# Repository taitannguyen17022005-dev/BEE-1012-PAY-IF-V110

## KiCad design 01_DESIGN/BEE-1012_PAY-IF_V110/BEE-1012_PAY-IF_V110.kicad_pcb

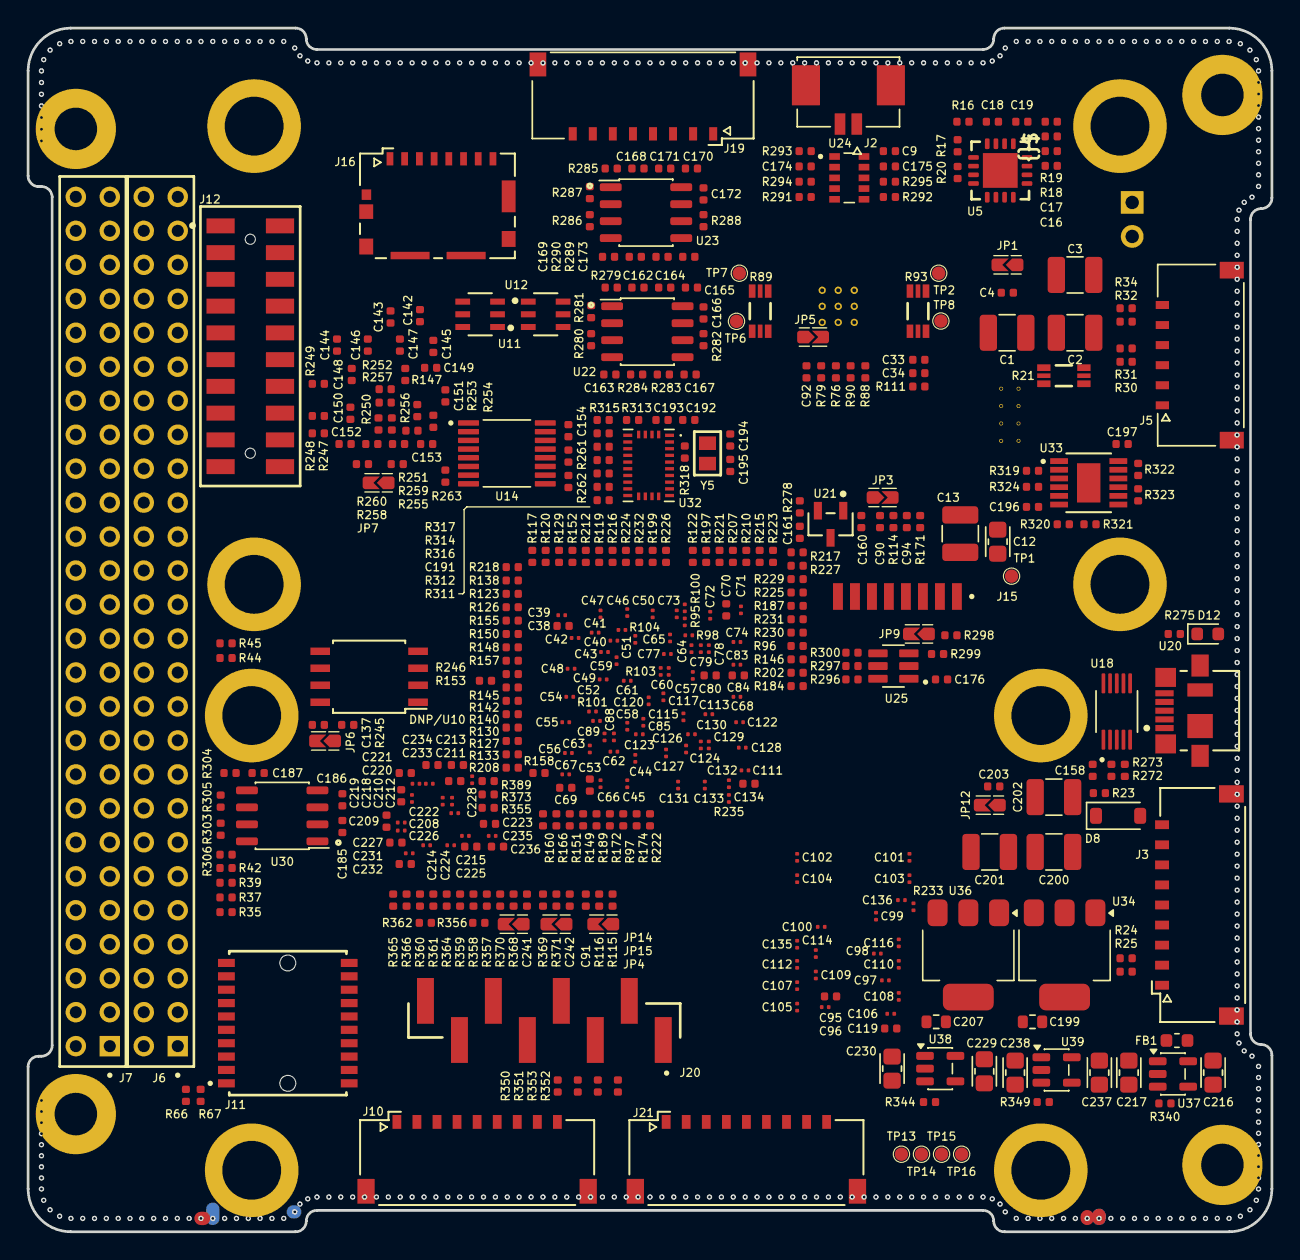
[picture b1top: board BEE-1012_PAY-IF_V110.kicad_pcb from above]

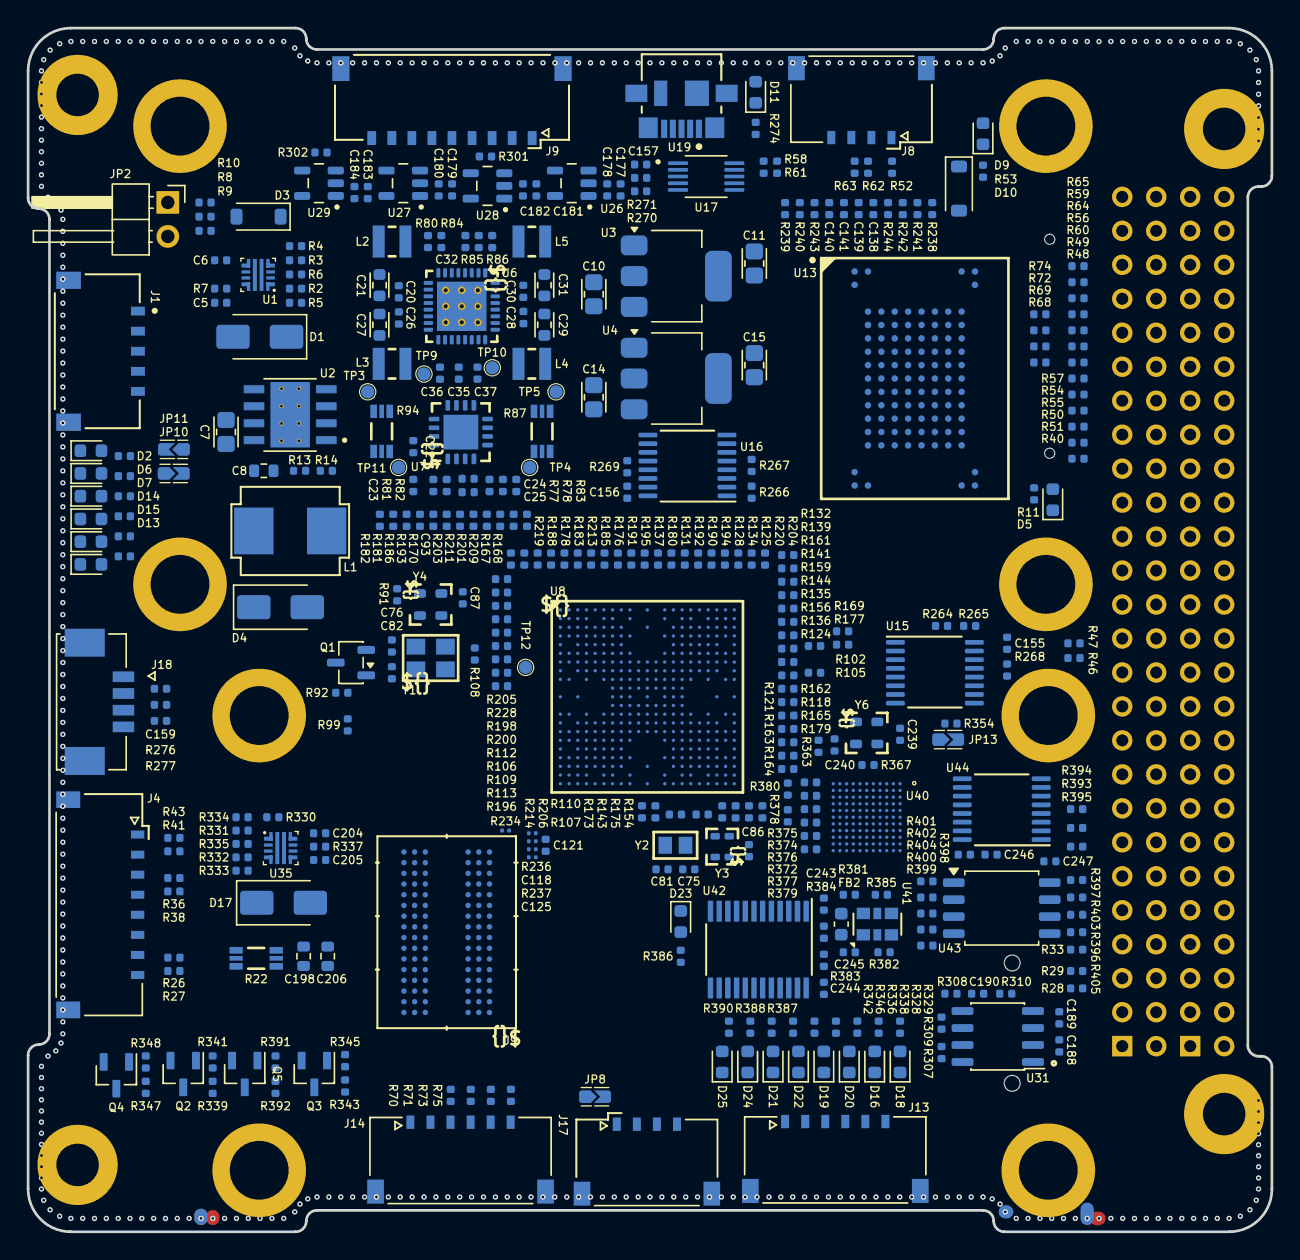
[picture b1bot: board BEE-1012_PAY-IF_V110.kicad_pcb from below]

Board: 8 copper layers, 93.0 x 90.0 mm, 803 parts (369 on the bottom side), 606 nets.

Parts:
C1, C2, C3, C13, C200, C201, C202: 47uF/25V; CAP_C_3225X80
C4, C140, C142, C160, C161, C164, C170, C176, C177, C179, C181, C183, C203: 1uF/20V; CAP_C_1005X50_L
C5, C6, C204, C205: 2.2nF/10V; CAP_C_1005X50_L
C7, C10, C11, C12, C14, C15: 10uF/20V; CAP_C_2012X110
C8: 0.01uF/16V; CAP_C_1608X80_L
C9, C16, C18, C22, C24, C32, C33, C34, C86, C87, C90, C91, C93, C94, C137, C138, C139, C141, C143, C146, C147, C148, C149, C150, C151, C152, C153, C154, C155, C156, C157, C158, C159, C162, C163, C165, C166, C167, C168, C169, C171, C172, C173, C174, C175, C185, C186, C187, C188, C189, C190, C191, C192, C193, C196, C197, C239, C240, C241, C242, C243, C244, C245, C246, C247: 0.1uF/10V; CAP_C_1005X50_L
C17, C19, C20, C23, C25, C26, C28, C30, C35, C36, C37, C38, C53, C69, C70, C80, C84, C95, C119, C121, C134, C144, C145, C209, C211, C213, C219, C221, C223, C225, C227, C232, C234, C236: 4.7uF/10V; CAP_C_1005X50_L
C21, C27, C29, C31: 22uF/10V; CAP_C_1608X80
C39, C40, C41, C42, C43, C44, C45, C46, C47, C48, C49, C50, C51, C52, C54, C55, C56, C57, C58, C59, C60, C61, C62, C63, C64, C65, C66, C67, C68, C71, C72, C73, C74, C77, C78, C79, C83, C85, C88, C89, C96, C97, C98, C99, C100, C101, C102, C103, C104, C105, C106, C107, C108, C109, C110, C111, C112, C113, C114, C115, C116, C117, C118, C120, C122, C123, C124, C125, C126, C127, C128, C129, C130, C131, C132, C133, C135, C136, C208, C210, C212, C214, C215, C218, C220, C222, C224, C226, C228, C231, C233, C235: 0.1uF/10V; CAP_C_0603x30
C75, C76, C81, C82, C194, C195: 18pF/10V; CAP_C_1005X50_L
C92: 2.2uF/10V; CAP_C_1005X50_L
C178, C180, C182, C184: 0.1uF/20V; CAP_C_1005X50_L
C198, C199, C206, C207: 10uF/20V; CAP_C_1608X80_L
C216, C217, C229, C230, C237, C238: 4.7uF/10V; CAP_C_2012X110
D1, D4, D17: SS54; D_SMA
D2, D15, D18, D25: LED_RED; LED_0603_1608Metric
D3, D8, D10: 1N4148W-TP; D_SOD-123
D5, D7, D14, D16, D19, D20, D21, D22, D23, D24: LED_GREEN; LED_0603_1608Metric
D6: LED_YELLOW; LED_0603_1608Metric
D9, D11, D12, D13: LED_BLUE; LED_0603_1608Metric
DNP/U10: AS3004204-0108X0PSAY; SOIC127P790X216-8
FB1, FB2: BLM18PG121SN1D; L_0603_1608Metric
H1, H2, H3, H4, H5, H6, H7, H8: 9774060360R; M4.4
Hole1, Hole2, Hole3, Hole4: hole_space; HEX-M3_NoVia
J1: 5040500591
J2: 0532610271; MOLEX_0532610271
J3, J9, J10, J21: 5040500991; MOLEX_5040500991
J4, J19: 5040500891; MOLEX_5040500891
J5, J13, J14: 5040500691; MOLEX_5040500691
J6, J7: ESQ-126-14-G-D
J8, J17: 5040500491; MOLEX_5040500491
J11: FSI-110-03-G-D-AD; SAMTEC_FSI-110-03-X-D-AD-TR
J12: TLE-110-01-G-DV-A-TR; SAMTEC-TLE-110-01-X-DV-A
J15: Header 8x1; PAD JTAG 1.27
J16: Molex_1051620001; MOLEX_1051620001
J18: 0532610471; MOLEX_0532610471
J20: HEADER 8x1; SAMTEC_TSM-108-01-L-SV-P-TR
JP1, JP8, JP9, JP10, JP11, JP12, JP13: Jumper_2_Bridged; JUMPER_1608
JP2: JUMPER_254P_NOPLACE; PinHeader_1x02_P2.54mm_Horizontal
JP3, JP7, JP15: Reset button; JUMPER_1608
JP4, JP14: User button; JUMPER_1608
JP5: nSTART button; JUMPER_1608
JP6: JUMPER_1608
L1: SRP7050TA-220M
L2, L3, L4, L5: DFE252012P-1R5M=P2; IND_C_1008
Q1: BSS138; SOT-23-3
Q2, Q3, Q4, Q5: MMBT2222A; SOT95P240X120-3N
R1, R66, R67, R77, R78, R245, R261, R262, R263, R264, R265, R266, R267, R270, R271, R272, R273, R293, R294, R295, R311, R312, R315, R316, R319, R320, R324, R350, R351, R352, R353, R389, R393, R394, R395, R399: 4.7k; RES_C_1005x30_L
R2, R331: 470k; RES_C_1005x30_L
R3, R4, R6, R152, R332, R333, R348: 47k; RES_C_1005x30_L
R5, R8, R13, R18, R19, R20, R52, R81, R82, R85, R86, R90, R91, R92, R115, R170, R171, R177, R238, R239, R240, R241, R242, R243, R244, R247, R248, R249, R250, R251, R252, R253, R254, R255, R256, R257, R260, R268, R269, R276, R277, R281, R284, R287, R290, R306, R310, R313, R334, R339, R340, R341, R343, R344, R345, R347, R349, R368, R369, R381, R382, R383, R384, R390, R391, R392, R398: 10k; RES_C_1005x30_L
R7, R337: 1.6k; RES_C_1005x30_L
R9, R11, R12, R15, R23, R53, R80, R258, R274, R275, R325, R326, R327, R328, R336, R338, R342, R346, R354, R363, R386, R387, R388: 1k; RES_C_1005x30_L
R10, R14, R329: 3.24k; RES_C_1005x30_L
R16, R17, R48, R49, R64, R65, R291, R292, R314, R317, R321, R396, R397, R400: DNP/4.7k; RES_C_1005x30_L
R21, R22, R87, R89, R93, R94: Shunt 4 Pin; RES_C_1206_SHUNT
R24, R25, R30, R31, R32, R34, R35, R37, R39, R42, R56, R57, R58, R59, R60, R61, R76, R79, R83, R106, R109, R355, R357, R358, R359, R360, R361, R364, R365, R366, R372, R373, R374, R375, R376, R377, R379, R401, R402, R403, R404, R405: 0R; RES_C_1005x30_L
R26, R27, R28, R29, R33, R36, R38, R40, R41, R43, R44, R45, R46, R47, R50, R51, R54, R55, R62, R63, R68, R69, R70, R71, R72, R73, R74, R75, R110, R111, R113: DNP/0R; RES_C_1005x30_L
R84: 100k; RES_C_1005x30_L
R88, R97, R167, R168, R169, R181, R182, R186, R193, R201, R203, R209, R211, R330: DNP/10k; RES_C_1005x30_L
R95, R98, R100: 200R; RES_C_0603X30
R96: 10K; RES_C_1005x30_L
R99, R114, R116, R259, R301, R302, R356, R362, R370, R371, R378, R380: 100R; RES_C_1005x30_L
R101, R104: 16.9k; RES_C_0603X30
R102: 20k; RES_C_1005x30_L
R103: 20k; RES_C_0603X30
R105: 4.02k; RES_C_1005x30_L
R107, R108: 1M 1%; RES_C_1005x30_L
R112, R367: DNP/22R; RES_C_1005x30_L
R117, R118, R119, R120, R121, R122, R123, R124, R125, R126, R127, R128, R129, R130, R131, R132, R133, R134, R135, R136, R137, R138, R139, R140, R141, R142, R143, R144, R145, R146, R147, R148, R149, R150, R151, R153, R154, R155, R156, R157, R158, R159, R160, R161, R162, R163, R164, R165, R166, R172, R173, R174, R175, R176, R178, R179, R180, R183, R184, R185, R187, R188, R189, R190, R191, R192, R194, R195, R196, R197, R198, R199, R200, R202, R204, R205, R206, R207, R208, R210, R212, R213, R214, R215, R216, R217, R218, R219, R220, R221, R222, R223, R224, R225, R226, R227, R228, R229, R230, R231, R232, R278, R279, R280, R282, R283, R285, R286, R288, R289, R296, R297, R300, R304, R308: 22R; RES_C_1005x30_L
R233, R235: 240R; RES_C_0603X30
R234: 100k; RES_C_0603X30
R236, R237: 1k; RES_C_0603X30
R246: 120R; RES_C_1005x30_L
R298, R299: 16.5k; RES_C_1005x30_L
R303, R305, R307, R309: 60R; RES_C_1005x30_L
R318: DNP/1M 1%; RES_C_1005x30_L
R322, R323: DNP/120R; RES_C_1005x30_L
R335: 133k; RES_C_1005x30_L
R385: DNP/100R; RES_C_1005x30_L
TP1, TP2, TP3, TP4, TP5, TP6, TP7, TP8, TP9, TP10, TP11, TP12, TP13, TP14, TP15, TP16: VALUE; Test point
U1, U35: TPS259470ARPWR; VQFN-HR-10
U2: TPS5430DDAR; CONV_TPS5430DDAR
U3, U4, U34, U36: LM1117MP-3.3/NOPB; SOT-223
U5: PAC1934; UQFN-16_4X4_EP2.6X2.6
U6: MCP16502 QFN-32; QFN-32_5X5_EP3.7X3.7
U7: Microchip PAC1934 UQFN-16; UQFN-16_4X4_EP2.6X2.6
U8: SAMA7G54; TFBGA-343_14x14 - 2.5mm
U9: IS43TR16512BL-125KBLI; TWBGA96_ISI
U11, U12: IP4220CZ6; DIODE_SOT457_1P7X3P1_NEX
U13: MTFC32GAZAQDW-AAT; BGA_100_C_100P_10X17_1400X1800X150
U14: SN74LV4052APWR; SOP65P640X120-16N
U15, U16, U44: SN3257QPWRQ1; SOIC_PRQ1_TEX
U17, U18: FSUSB42MUX; SOP50P490X110-10N
U19, U20: 473460001; 47346-0001_MOL
U21: TC1047AVNBTR; SOT-23_MC_MCH
U22, U23: OPA2340; SOIC127P602X173-8N
U24: RV-3129-C3-32.768KHZ-OPTION-A-TB-QA; IC_RV-3129-C3-32.768KHZ-OPTION-A-TB-QA
U25: TPL5010DDCR
U26, U27: DS90LV011AQ-Q1
U28, U29: DS90LT012AQ-Q1; DS90LV011AQ-Q1
U30, U31: SN65HVD230DR; SOIC127P602X173-8N
U32: BNO086; IC_BNO086
U33: LTC2865HMSE#TRPBF; MSOP-12_MSE_LIT
U37, U38: TLV75518PDBVR; SOT-23-5
U39: TLV75510PDBVR; SOT-23-5
U40: LFD2NX-17-7MG121I; csfBGA121_LAT
U41: DSC1123CI1-050.0000; VDFN6_3P2X2P5_MCH
U42: SN74AXCH8T245PWR; SOP65P640X120-24N
U43: S25FL128LAGMFI010; SOIC-8_5.3x5.3mm_P1.27mm
Y1: 24MHz; CRYSTAL_ABM8G
Y2, Y5: 32.768kHz; CRYSTAL_NX2012SA
Y3: 32.768KHz; DFN-4_2x1.6
Y4, Y6: DSC10xx DFN-4; DFN-4_2.5x2

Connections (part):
1V8_VCCAUX: C208.2, C209.1, C210.2, C211.1, C212.2, C213.1, C214.2, C215.2, C216.1, R339.2, U37.5 (OUT), U40.C6 (VCCAUXA), U40.D9 (VCCAUXH5), U40.F3 (VCCAUX), U40.H3 (VCCAUXH3), U40.H8 (VCCAUXH4)
1V8_VCCIO3/4/5: C222.2, C223.1, C224.2, C225.1, C226.2, C227.1, C228.2, C229.1, C243.2, R343.2, R368.2, R369.2, R381.1, U38.5 (OUT), U40.E8 (VCCIO5), U40.J6 (VCCIO3), U40.J9 (VCCIO4), U40.K3 (VCCIO3), U42.1 (VCCA)
1V_VCORE: C231.2, C232.1, C233.2, C234.1, C235.2, C236.1, C237.1, R347.2, U39.5 (OUT), U40.C10 (VCC), U40.E4 (VCC), U40.G6 (VCCECLK)
3.3_VBAT: C9.2, C175.2, J2.1, R111.1, U24.9 (VBACKUP)
3V3_COM: C15.1, C154.2, C155.2, C156.2, C157.2, C158.2, C159.2, C160.2, C164.2, C165.2, C170.2, C171.2, C174.2, C176.2, C177.2, C178.2, C179.2, C180.2, C181.2, C182.2, C183.2, C184.2, C185.2, C186.2, C188.2, C189.2, C192.2, C193.2, C196.2, C197.2, C244.2, C246.2, C247.2, J11.03, J11.04, J11.17, J11.18, J12.2, J18.1, J19.1, J19.3, J19.5, J19.7, R15.1, R48.2, R49.2, R64.2, R65.2, R66.2, R67.2, R264.1, R265.1, R266.1, R267.1, R276.1, R277.1, R291.1, R292.1, R293.1, R294.1, R295.1, R311.1, R312.1, R313.1, R314.1, R315.1, R319.1, R320.1, R393.1, R394.1, R395.1, R396.1, R397.1, R399.1, R400.1, U4.2 (VOUT_2), U4.4 (VOUT_4), U14.16 (VCC), U15.16 (VDD), U16.16 (VDD), U17.1 (VCC), U18.1 (VCC)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
3V3_FPGADN: C207.1, C230.1, C238.1, R336.1, R342.1, R344.1, R346.1, R349.1, U36.2 (VOUT_2), U36.4 (VOUT_4), U38.1 (IN), U39.1 (IN)
3V3_FPGAUP: C199.1, C217.1, FB1.2, R328.1, R338.1, R340.1, U34.2 (VOUT_2), U34.4 (VOUT_4), U37.1 (IN)
3V3_VCCIO0/1: C218.2, C219.1, C220.2, C221.1, C239.1, C240.2, C245.2, FB1.1, FB2.2, J20.2, R350.1, R351.1, R352.1, R354.1, R363.1, R382.2, R387.1, R388.1, R389.1, R390.2, R392.2, U40.D2 (VCCIO1), U40.D4 (VCCIO0), Y6.4 (VDD)
3V3_eMMC: C11.1, C138.2, C139.2, C140.2, C141.2, C144.1, C145.1, C146.2, C147.2, C148.2, C149.2, C150.2, C151.2, C152.2, C153.2, J16.P4 (VDD), R11.1, R238.1, R239.1, R240.1, R241.1, R242.1, R243.1, R244.1, R247.1, R248.1, R249.1, R250.1, R251.1, R252.1, R253.1, R254.1, R255.1, R256.1, R257.1, R258.1, U3.2 (VOUT_2), U3.4 (VOUT_4), U11.5 (VBUS), U12.5 (VBUS), U13.F2 (VCC), U13.F3 (VCC), U13.F4 (VCC), U13.F5 (VCC), U13.F6 (VCC), U13.F7 (VCC), U13.F8 (VCC), U13.F9 (VCC), U13.H3 (VCCQ), U13.H8 (VCCQ), U13.L2 (VCCQ), U13.L4 (VCCQ), U13.L7 (VCCQ), U13.L9 (VCCQ), U13.P3 (VCCQ), U13.P8 (VCCQ)
5V: C10.1, C12.1, C13.1, C14.1, C20.1, C26.1, C28.1, C30.1, C32.2, C35.1, C202.1, C203.2, JP8.1 (A), JP12.1 (A), L1.2, R12.1, R13.1, R88.1, R169.1, R330.1, R331.1, TP1.1 (1_1), U3.3 (VIN), U4.3 (VIN), U6.4 (SVIN), U6.10 (PVIN1), U6.15 (PVIN2), U6.20 (LVIN), U6.26 (PVIN3), U6.31 (PVIN4), U35.5 (IN)
5V_FPGA: C198.1, C206.1, R22.2, U34.3 (VIN), U36.3 (VIN)
5V_FPGA_efuse: C200.1, C201.1, D17.1 (K), JP12.2 (B), R22.1, R329.1, R332.1, R333.1, U35.6 (OUT)
12V: C7.1, R21.2, U2.7 (VIN)
12V_CONN: C3.1, C4.2, J1.1, J1.2, J3.1, J3.2, J3.3, JP1.1 (A), R2.1, R8.1, U1.5 (IN)
12V_efuse: C1.1, C2.1, D1.1 (K), JP1.2 (B), R1.1, R3.1, R4.1, R21.1, U1.6 (OUT)
/CONNECTOR_EXP/EXP_ON_IF: D8.2 (A), J3.7
/CONNECTOR_EXP/EXP_USB_N: J4.8, R25.1, R27.1
/CONNECTOR_EXP/EXP_USB_P: J4.7, R24.1, R26.1
/CONNECTOR_INTERFACE/CLK_EXP_CONNECTOR: J14.4, R71.2
/CONNECTOR_INTERFACE/CONN_422_RX_N: J5.5, R32.2
/CONNECTOR_INTERFACE/CONN_422_RX_P: J5.6, R34.2
/CONNECTOR_INTERFACE/CONN_422_TX_N: J5.4, R31.2
/CONNECTOR_INTERFACE/CONN_422_TX_P: J5.3, R30.2
/CONNECTOR_INTERFACE/CS_EXP_CONNECTOR: J14.3, R70.2
/CONNECTOR_INTERFACE/IF_USB_CONN_N: J8.2, R58.2, R62.2
/CONNECTOR_INTERFACE/IF_USB_CONN_P: J8.3, R61.2, R63.2
/CONNECTOR_INTERFACE/MISO_EXP_CONNECTOR: J14.6, R75.2
/CONNECTOR_INTERFACE/MOSI_EXP_CONNECTOR: J14.5, R73.2
/CONNECTOR_INTERFACE/SCL_EXP_CONNECTOR: J13.5, J13.6, R72.2, R74.2
/CONNECTOR_INTERFACE/SDA_EXP_CONNECTOR: J13.1, J13.2, R68.2, R69.2
/FPGA_PART1/JTAG_EN: JP13.2 (B), R354.2, U40.A1 (JTAG_EN)
/FPGA_PART1/JTAG_TCK: J20.5, R353.1, U40.C1 (PR9A)
/FPGA_PART1/JTAG_TDI: J20.4, R352.2, U40.A3 (PR5A)
/FPGA_PART1/JTAG_TDO: J20.7, R351.2, U40.A2 (PR5B)
/FPGA_PART1/JTAG_TMS: J20.8, R350.2, U40.B1 (PR3B)
/FPGA_POWER/AUXOFF: R332.2, U35.3 (PG/AUXOFF)
/FPGA_POWER/~FLT: R333.2, U35.4 (PGTH/~FLT)
/IMU/BNO_PS0: R314.2, R316.1, U32.6 (PS0/WAKE)
/IMU/BNO_PS1: R315.2, R317.1, U32.5 (PS1)
/IMU/BNO_XIN32: C194.1, R318.1, U32.27 (XIN32), Y5.2
/IMU/BNO_XOUT32: C195.1, R318.2, U32.26 (XOUT32/CLKSEL1), Y5.1
/POWER/AUXOFF: R3.2, U1.3 (PG/AUXOFF)
/POWER/~FLT: R4.2, U1.4 (PGTH/~FLT)
/POWER_MEASUREMENT/SENSE_5V_FPGA_N: R22.4, U5.14 (SENSE2-)
/POWER_MEASUREMENT/SENSE_5V_FPGA_P: R22.3, U5.13 (SENSE2+)
/POWER_MEASUREMENT/SENSE_12V_EXP_N: R21.4, U5.12 (SENSE1-)
/POWER_MEASUREMENT/SENSE_12V_EXP_P: R21.3, U5.11 (SENSE1+)
/SAMA7G54_DDR3L/DDR_A0: U8.W6 (DDR_A0), U9.N3 (A0)
/SAMA7G54_DDR3L/DDR_A1: U8.P6 (DDR_A1), U9.P7 (A1)
/SAMA7G54_DDR3L/DDR_A2: U8.V5 (DDR_A2), U9.P3 (A2)
/SAMA7G54_DDR3L/DDR_A3: U8.V6 (DDR_A3), U9.N2 (A3)
/SAMA7G54_DDR3L/DDR_A4: U8.R6 (DDR_A4), U9.P8 (A4)
/SAMA7G54_DDR3L/DDR_A5: U8.W4 (DDR_A5), U9.P2 (A5)
/SAMA7G54_DDR3L/DDR_A6: U8.P7 (DDR_A6), U9.R8 (A6)
/SAMA7G54_DDR3L/DDR_A7: U8.W2 (DDR_A7), U9.R2 (A7)
/SAMA7G54_DDR3L/DDR_A8: U8.L8 (DDR_A8), U9.T8 (A8)
/SAMA7G54_DDR3L/DDR_A9: U8.V4 (DDR_A9), U9.R3 (A9)
/SAMA7G54_DDR3L/DDR_A10: U8.T3 (DDR_A10), U9.L7 (A10/AP)
/SAMA7G54_DDR3L/DDR_A11: U8.M9 (DDR_A11), U9.R7 (A11)
/SAMA7G54_DDR3L/DDR_A12: U8.P5 (DDR_A12), U9.N7 (A12/BC#)
/SAMA7G54_DDR3L/DDR_A13: U8.V2 (DDR_A13), U9.T3 (A13)
/SAMA7G54_DDR3L/DDR_A14: U8.L9 (DDR_A14), U9.T7 (A14)
/SAMA7G54_DDR3L/DDR_A15: U8.R4 (DDR_A15), U9.M7 (A15)
/SAMA7G54_DDR3L/DDR_BA0: U8.V8 (DDR_BA0), U9.M2 (BA0)
/SAMA7G54_DDR3L/DDR_BA1: U8.P4 (DDR_BA1), U9.N8 (BA1)
/SAMA7G54_DDR3L/DDR_BA2: U8.R8 (DDR_BA2), U9.M3 (BA2)
/SAMA7G54_DDR3L/DDR_CAS: U8.T8 (DDR_CAS#), U9.K3 (CAS#)
/SAMA7G54_DDR3L/DDR_CKE: U8.V3 (DDR_CKE), U9.K9 (CKE)
/SAMA7G54_DDR3L/DDR_CK_N: U8.T4 (DDR_CLK_N), U9.K7 (CK#)
/SAMA7G54_DDR3L/DDR_CK_P: U8.U4 (DDR_CLK_P), U9.J7 (CK)
/SAMA7G54_DDR3L/DDR_CS: U8.V7 (DDR_CS#), U9.L2 (CS#)
/SAMA7G54_DDR3L/DDR_D0: U8.N2 (DDR_D0), U9.E3 (DQL0)
/SAMA7G54_DDR3L/DDR_D1: U8.M7 (DDR_D1), U9.F7 (DQL1)
/SAMA7G54_DDR3L/DDR_D2: U8.R3 (DDR_D2), U9.F2 (DQL2)
/SAMA7G54_DDR3L/DDR_D3: U8.M8 (DDR_D3), U9.F8 (DQL3)
/SAMA7G54_DDR3L/DDR_D4: U8.T2 (DDR_D4), U9.H3 (DQL4)
/SAMA7G54_DDR3L/DDR_D5: U8.N8 (DDR_D5), U9.H8 (DQL5)
/SAMA7G54_DDR3L/DDR_D6: U8.T1 (DDR_D6), U9.G2 (DQL6)
/SAMA7G54_DDR3L/DDR_D7: U8.N7 (DDR_D7), U9.H7 (DQL7)
/SAMA7G54_DDR3L/DDR_D8: U8.Y7 (DDR_D8), U9.D7 (DQU0)
/SAMA7G54_DDR3L/DDR_D9: U8.AA4 (DDR_D9), U9.C3 (DQU1)
/SAMA7G54_DDR3L/DDR_D10: U8.Y9 (DDR_D10), U9.C8 (DQU2)
/SAMA7G54_DDR3L/DDR_D11: U8.Y3 (DDR_D11), U9.C2 (DQU3)
/SAMA7G54_DDR3L/DDR_D12: U8.AA7 (DDR_D12), U9.A7 (DQU4)
/SAMA7G54_DDR3L/DDR_D13: U8.AA3 (DDR_D13), U9.A2 (DQU5)
/SAMA7G54_DDR3L/DDR_D14: U8.W7 (DDR_D14), U9.B8 (DQU6)
/SAMA7G54_DDR3L/DDR_D15: U8.W3 (DDR_D15), U9.A3 (DQU7)
/SAMA7G54_DDR3L/DDR_DQM0: U8.N1 (DDR_DQM0), U9.E7 (DML)
/SAMA7G54_DDR3L/DDR_DQM1: U8.Y4 (DDR_DQM1), U9.D3 (DMU)
/SAMA7G54_DDR3L/DDR_DQS0_N: U8.R2 (DDR_DQS0_N), U9.G3 (DQSL#)
/SAMA7G54_DDR3L/DDR_DQS0_P: U8.R1 (DDR_DQS0_P), U9.F3 (DQSL)
/SAMA7G54_DDR3L/DDR_DQS1_N: U8.AA6 (DDR_DQS1_N), U9.B7 (DQSU#)
/SAMA7G54_DDR3L/DDR_DQS1_P: U8.Y6 (DDR_DQS1_P), U9.C7 (DQSU)
/SAMA7G54_DDR3L/DDR_ODT: U8.W1 (DDR_ODT), U9.K1 (ODT)
/SAMA7G54_DDR3L/DDR_RAS: U8.U8 (DDR_RAS#), U9.J3 (RAS#)
/SAMA7G54_DDR3L/DDR_RESET: R234.1, U8.V1 (DDR_RESET#), U9.T2 (RESET#)
/SAMA7G54_DDR3L/DDR_VREF: C111.2, C118.1, C125.2, C135.2, C136.2, R236.2, R237.1, U8.Y1 (DDR_VREF), U9.H1 (VREFDQ), U9.M8 (VREFCA)
/SAMA7G54_DDR3L/DDR_WE: U8.N10 (DDR_WE#), U9.L3 (WE#)
/SAMA7G54_DDR3L/DDR_ZQ: R235.1, U8.AA2 (DDR_ZQ)
/SAMA7G54_MPU/XIN: R106.2, R112.2, TP12.1 (1_1), U8.J2 (XIN)
/SAMA7G54_MPU/XIN32: C75.1, R107.1, R110.2, U8.Y13 (XIN32), Y2.2
/SAMA7G54_MPU/XIN_24M: C76.1, R106.1, R108.1, Y1.3 (Osc2)
/SAMA7G54_MPU/XOUT: R109.2, R113.2, U8.J1 (XOUT)
/SAMA7G54_MPU/XOUT32: C81.1, R107.2, U8.AA13 (XOUT32), Y2.1
/SAMA7G54_MPU/XOUT_24M: C82.1, R108.2, R109.1, Y1.1 (Osc1)
/SAMA7G54_PIO/NTRST_PC25: C93.2, J15.6, R170.2, U8.B1 (PC25)
/SAMA7G54_PIO/PA0: R117.1, U8.H17 (PA0)
/SAMA7G54_PIO/PA1: R120.1, U8.G20 (PA1)
/SAMA7G54_PIO/PA2: R123.1, U8.L13 (PA2)
/SAMA7G54_PIO/PA3: R126.1, U8.L14 (PA3)
/SAMA7G54_PIO/PA4: R129.1, U8.K13 (PA4)
/SAMA7G54_PIO/PA5: R132.1, U8.C21 (PA5)
/SAMA7G54_PIO/PA6: R135.1, U8.K14 (PA6)
/SAMA7G54_PIO/PA7: R138.1, U8.H16 (PA7)
/SAMA7G54_PIO/PA8: R139.1, U8.B21 (PA8)
/SAMA7G54_PIO/PA9: R141.1, U8.D20 (PA9)
/SAMA7G54_PIO/PA10: R144.1, U8.J15 (PA10)
/SAMA7G54_PIO/PA11: R147.1, R152.1, U8.F20 (PA11)
/SAMA7G54_PIO/PA12: R149.1, U8.V14 (PA12)
/SAMA7G54_PIO/PA13: R151.1, U8.AA16 (PA13)
/SAMA7G54_PIO/PA14: R154.1, U8.AA20 (PA14)
/SAMA7G54_PIO/PA17: R158.1, U8.V16 (PA17)
/SAMA7G54_PIO/PA18: R160.1, U8.Y16 (PA18)
/SAMA7G54_PIO/PA19: R162.1, U8.V20 (PA19)
/SAMA7G54_PIO/PA20: R164.1, U8.Y21 (PA20)
/SAMA7G54_PIO/PA21: R165.1, U8.V21 (PA21)
/SAMA7G54_PIO/PA22: R166.1, U8.Y18 (PA22)
/SAMA7G54_PIO/PA26: R172.1, U8.W16 (PA26)
/SAMA7G54_PIO/PA27: R173.1, U8.W18 (PA27)
/SAMA7G54_PIO/PA28: R174.1, U8.T14 (PA28)
/SAMA7G54_PIO/PA29: R175.1, U8.W19 (PA29)
/SAMA7G54_PIO/PA31: R179.1, U8.W20 (PA31)
/SAMA7G54_PIO/PB0: R118.1, U8.U18 (PB0)
/SAMA7G54_PIO/PB1: R121.1, U8.W21 (PB1)
/SAMA7G54_PIO/PB2: R124.1, U8.T21 (PB2)
/SAMA7G54_PIO/PB3: R127.1, U8.V19 (PB3)
/SAMA7G54_PIO/PB4: R130.1, U8.T20 (PB4)
/SAMA7G54_PIO/PB5: R133.1, U8.V18 (PB5)
/SAMA7G54_PIO/PB6: R136.1, U8.T19 (PB6)
/SAMA7G54_PIO/PB8: R140.1, U8.T18 (PB8)
/SAMA7G54_PIO/PB9: R142.1, U8.P17 (PB9)
/SAMA7G54_PIO/PB10: R145.1, U8.P15 (PB10)
/SAMA7G54_PIO/PB11: R148.1, U8.G21 (PB11)
/SAMA7G54_PIO/PB12: R150.1, U8.M15 (PB12)
/SAMA7G54_PIO/PB13: R153.1, U8.R16 (PB13)
/SAMA7G54_PIO/PB14: R155.1, U8.N14 (PB14)
/SAMA7G54_PIO/PB15: R156.1, U8.N15 (PB15)
/SAMA7G54_PIO/PB16: R157.1, U8.M14 (PB16)
/SAMA7G54_PIO/PB17: R159.1, U8.F21 (PB17)
/SAMA7G54_PIO/PB18: R161.1, U8.D21 (PB18)
/SAMA7G54_PIO/PB19: R163.1, U8.M13 (PB19)
/SAMA7G54_PIO/PB28: R167.2, R168.1, U8.G10 (PB28)
/SAMA7G54_PIO/PB29: R176.1, U8.H11 (PB29)
/SAMA7G54_PIO/PB30: R178.1, U8.B9 (PB30)
/SAMA7G54_PIO/PB31: R180.1, U8.A13 (PB31)
/SAMA7G54_PIO/PC0: R183.1, U8.A9 (PC0)
/SAMA7G54_PIO/PC1: R185.1, U8.H10 (PC1)
/SAMA7G54_PIO/PC2: R188.1, U8.A7 (PC2)
/SAMA7G54_PIO/PC3: R186.2, R193.1, U8.G1 (PC3)
/SAMA7G54_PIO/PC4: R191.1, U8.H5 (PC4)
/SAMA7G54_PIO/PC5: R181.2, R182.1, U8.F2 (PC5)
/SAMA7G54_PIO/PC7: R196.1, U8.J8 (PC7)
/SAMA7G54_PIO/PC8: R198.1, U8.F1 (PC8)
/SAMA7G54_PIO/PC9: R200.1, U8.G2 (PC9)
/SAMA7G54_PIO/PC10: R202.1, U8.M10 (PC10)
/SAMA7G54_PIO/PC12: R205.1, U8.D1 (PC12)
/SAMA7G54_PIO/PC13: R207.1, U8.F8 (PC13)
/SAMA7G54_PIO/PC14: R210.1, U8.D6 (PC14)
/SAMA7G54_PIO/PC15: R213.1, U8.H9 (PC15)
/SAMA7G54_PIO/PC16: R215.1, U8.D5 (PC16)
/SAMA7G54_PIO/PC17: R217.1, U8.D3 (PC17)
/SAMA7G54_PIO/PC18: R219.1, U8.C4 (PC18)
/SAMA7G54_PIO/PC19: R221.1, U8.G8 (PC19)
/SAMA7G54_PIO/PC20: R223.1, U8.D4 (PC20)
/SAMA7G54_PIO/PC21: R225.1, U8.E4 (PC21)
/SAMA7G54_PIO/PC22: R227.1, U8.C3 (PC22)
/SAMA7G54_PIO/PC23: R228.1, U8.F3 (PC23)
/SAMA7G54_PIO/PC24: R229.1, U8.C2 (PC24)
/SAMA7G54_PIO/PC30: R230.1, U8.G4 (PC30)
/SAMA7G54_PIO/PC31: R231.1, U8.D2 (PC31)
/SAMA7G54_PIO/PD0: R184.1, U8.G3 (PD0)
/SAMA7G54_PIO/PD1: R187.1, U8.F4 (PD1)
/SAMA7G54_PIO/PD2: R189.1, U8.H12 (PD2)
/SAMA7G54_PIO/PD3: R190.1, U8.B15 (PD3)
/SAMA7G54_PIO/PD4: R192.1, U8.A15 (PD4)
/SAMA7G54_PIO/PD5: R194.1, U8.A16 (PD5)
/SAMA7G54_PIO/PD6: R195.1, U8.G12 (PD6)
/SAMA7G54_PIO/PD7: R197.1, U8.J11 (PD7)
/SAMA7G54_PIO/PD8: R199.1, U8.B13 (PD8)
/SAMA7G54_PIO/PD11: R204.1, U8.A20 (PD11)
/SAMA7G54_PIO/PD12: R206.1, U8.P12 (PD12)
/SAMA7G54_PIO/PD13: R208.1, U8.H18 (PD13)
/SAMA7G54_PIO/PD14: R212.1, U8.C19 (PD14)
/SAMA7G54_PIO/PD15: R214.1, U8.R12 (PD15)
/SAMA7G54_PIO/PD16: R216.1, U8.D18 (PD16)
/SAMA7G54_PIO/PD17: R218.1, U8.G18 (PD17)
/SAMA7G54_PIO/PD18: R220.1, U8.B19 (PD18)
/SAMA7G54_PIO/PD19: R222.1, U8.N11 (PD19)
/SAMA7G54_PIO/PD20: R224.1, U8.C18 (PD20)
/SAMA7G54_PIO/PD21: R226.1, U8.F18 (PD21)
/SAMA7G54_PIO/PD31: R232.1, U8.C16 (PD31)
/SAMA7G54_PIO/PE0: R119.1, U8.E18 (PE0)
/SAMA7G54_PIO/PE1: R122.1, U8.F14 (PE1)
/SAMA7G54_PIO/PE2: R125.1, U8.A18 (PE2)
/SAMA7G54_PIO/PE3: R128.1, U8.C15 (PE3)
/SAMA7G54_PIO/PE4: R131.1, U8.D15 (PE4)
/SAMA7G54_PIO/PE5: R134.1, U8.B16 (PE5)
/SAMA7G54_PIO/PE6: R137.1, U8.G13 (PE6)
/SAMA7G54_PIO/TCK_SWCLK_PC26: J15.5, U8.H7 (PC26)
/SAMA7G54_PIO/TDI_PC28: J15.4, U8.H6 (PC28)
/SAMA7G54_PIO/TDO_PC29: J15.7, U8.A2 (PC29)
/SAMA7G54_PIO/TMS_SWDIO_PC27: J15.8, U8.C1 (PC27)
/SAMA7G54_PMIC/SENSE1_N: R93.4, U7.12 (SENSE1-)
/SAMA7G54_PMIC/SENSE1_P: R93.3, U7.11 (SENSE1+)
/SAMA7G54_PMIC/SENSE2_N: R94.4, U7.14 (SENSE2-)
/SAMA7G54_PMIC/SENSE2_P: R94.3, U7.13 (SENSE2+)
/SAMA7G54_PMIC/SENSE3_N: R87.4, U7.7 (SENSE3-)
/SAMA7G54_PMIC/SENSE3_P: R87.3, U7.8 (SENSE3+)
/SAMA7G54_PMIC/SENSE4_N: R89.4, U7.9 (SENSE4-)
/SAMA7G54_PMIC/SENSE4_P: R89.3, U7.10 (SENSE4+)
ADC_ILM: R7.1, R215.2, U1.9 (ILM)
ADC_TEMP1: C166.2, R184.2, R282.2
ADC_TEMP2: C162.2, R187.2, R279.2
ADC_TEMP3: C168.2, R225.2, R285.2
ADC_TEMP4: C172.2, R227.2, R288.2
ADC_TEMP_1: C161.2, R223.2, R278.2
BNO_BOOT: R226.2, R313.2, U32.4 (BOOTN)
BNO_INT: R199.2, U32.14 (H_INTN)
BUS_3V3: J7.27, J7.28
BUS_5V: J7.25, J7.26
CAN_H_AX100U: J11.07, R29.1, R307.1, U31.7 (CANH)
CAN_H_main: J3.9, J6.03, R29.2, R303.1, U30.7 (CANH)
CAN_L_AX100U: J11.08, R28.1, R309.2, U31.6 (CANL)
CAN_L_main: J3.8, J6.01, R28.2, R305.2, U30.6 (CANL)
COM_UART_RX: R229.2, U14.3 (2-COM)
COM_UART_SEL_CHANNEL_A: R166.2, R261.1, U14.10 (A)
COM_UART_SEL_CHANNEL_B: R160.2, R262.1, U14.9 (B)
COM_UART_TX: R228.2, U14.13 (1-COM)
EXP_2_CONN_USB_N: R27.2, R62.1
EXP_2_CONN_USB_P: R26.2, R63.1
EXP_2_IF_USB_N: R25.2, U18.4 (D-)
EXP_2_IF_USB_P: R24.2, U18.3 (D+)
EXP_RS422_PASSTHR_RX+: J4.1, R39.1, R43.1, R51.2
EXP_RS422_PASSTHR_RX-: J4.2, R41.1, R42.1, R50.1
EXP_RS422_PASSTHR_TX+: J4.3, R35.1, R36.1
EXP_RS422_PASSTHR_TX-: J4.4, R37.1, R38.1
FLASH_SPI_MCLK: R396.2, U43.6 (SCK), U44.7 (D2)
FLASH_SPI_MCSN: R401.1, U44.4 (D1)
FLASH_SPI_MD2: R404.1, U40.C5 (PT63B)
FLASH_SPI_MD3: R403.2, U40.C9 (PT65A)
FLASH_SPI_MISO/MD1: R402.1, U44.12 (D4)
FLASH_SPI_MOSI/MD0: R405.2, U44.9 (D3)
FPGA_DOWNLOAD_DONE: R163.2, R391.2, R392.1, U40.D10 (PT59B)
FPGA_DOWNLOAD_INITN: D25.1 (K), R157.2, R390.1, U40.B4 (PT57A)
FPGA_DOWNLOAD_PROGRAMN: R158.2, R389.2, U40.C4 (PT57B)
FPGA_FLASH_SPI_MCLK: U40.D11 (PT59A), U44.6 (S2B)
FPGA_FLASH_SPI_MCSN: R394.2, U40.D7 (PT61A), U44.3 (S1B)
FPGA_FLASH_SPI_MISO/MD1: U40.D5 (PT63A), U44.13 (S4B)
FPGA_FLASH_SPI_MOSI/MD0: U40.D6 (PT61B), U44.10 (S3B)
FPGA_HEATBEAT: U40.K11 (PB40B), U42.10 (A8)
FPGA_INT_ERROR: U40.K10 (PB40A), U42.9 (A7)
FPGA_LVDS_RXC_N: J10.9, R356.1, R357.2
FPGA_LVDS_RXC_P: J10.8, R356.2, R358.2
FPGA_LVDS_RXD_N: J10.4, R361.2, R362.2
FPGA_LVDS_RXD_P: J10.3, R360.2, R362.1
FPGA_LVDS_TXC_N: J10.7, R359.2
FPGA_LVDS_TXC_P: J10.6, R364.2
FPGA_LVDS_TXD_N: J10.2, R366.2
FPGA_LVDS_TXD_P: J10.1, R365.2
FPGA_SPARE_IN1: U40.J10 (PB48A), U42.5 (A3)
FPGA_SPARE_IN2: U40.J11 (PB48B), U42.6 (A4)
FPGA_SPI_RX_AVAIL: U40.H10 (PB44B), U42.8 (A6)
FPGA_SPI_RX_CLK: U15.6 (S2B), U40.C2 (PR7B)
FPGA_SPI_RX_CSN: U40.J7 (PB42B), U42.4 (A2)
FPGA_SPI_RX_MISO: U15.13 (S4B), U40.D1 (PR9B)
FPGA_SPI_RX_MOSI: U15.10 (S3B), U40.B2 (PR7A)
FPGA_SPI_TX_CLK: U16.6 (S2B), U40.E1 (PR11B)
FPGA_SPI_TX_CSN: U40.J8 (PB42A), U42.3 (A1)
FPGA_SPI_TX_MISO: U16.13 (S4B), U40.F1 (PR13B)
FPGA_SPI_TX_MOSI: U16.10 (S3B), U40.E2 (PR11A)
FPGA_SPI_TX_READY: U40.H11 (PB44A), U42.7 (A5)
FPGA_UART_RX: R220.2, U40.D8 (PT65B)
FPGA_UART_TX: R222.2, U40.C3 (PT67B)
FPGA_USER_BUTTON: R370.1, U40.G8 (PB54B)
FPGA_nRST_BUTTON: R371.1, U40.G9 (PB54A)
GND: C1.2, C2.2, C3.2, C4.1, C5.1, C6.1, C7.2, C9.1, C10.2, C11.2, C12.2, C13.2, C14.2, C15.2, C16.1, C17.2, C18.1, C19.2, C20.2, C21.2, C22.1, C23.2, C24.1, C25.2, C26.2, C27.2, C28.2, C29.2, C30.2, C31.2, C32.1, C33.1, C34.1, C35.2, C36.2, C37.2, C38.1, C39.2, C40.2, C41.2, C42.2, C43.2, C44.2, C45.2, C46.2, C47.2, C48.2, C49.2, C50.2, C51.2, C52.2, C53.1, C54.2, C55.2, C56.2, C57.1, C58.2, C59.2, C60.2, C61.2, C62.2, C63.2, C64.2, C65.2, C66.2, C67.2, C68.2, C69.1, C70.1, C71.2, C72.2, C73.2, C74.2, C75.2, C76.2, C77.2, C78.2, C79.2, C80.1, C81.2, C82.2, C83.2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
GOM_VBAT: J7.45, J7.46
I2C_SCL_EXP_PC104: J4.6, R59.1, R74.1
I2C_SCL_IF: R49.1, R60.2, R72.1, R221.2
I2C_SDA_EXP_PC104: J4.5, R56.1, R69.1
I2C_SDA_IF: R48.1, R57.2, R68.1, R219.2
IF_INPUT_USB_N: U8.B4 (HHSB_DM), U18.6 (HSD1-)
IF_INPUT_USB_P: U8.A4 (HHSB_DP), U18.7 (HSD1+)
IF_OUTPUT_USB_N: U8.B3 (HHSA_DM), U17.4 (D-)
IF_OUTPUT_USB_P: U8.A3 (HHSA_DP), U17.3 (D+)
IF_OUT_CONN_USB_N: R58.1, U17.6 (HSD1-)
IF_OUT_CONN_USB_P: R61.1, U17.7 (HSD1+)
LPM: Q1.1 (G), R76.1, R92.1, R99.1
LVDS_SPI_RX_CLK: R179.2, U15.7 (D2)
LVDS_SPI_RX_CSN: R118.2, U15.4 (D1)
LVDS_SPI_RX_MISO: R121.2, U15.12 (D4)
LVDS_SPI_RX_MOSI: R124.2, U15.9 (D3)
LVDS_SPI_TX_CLK: R134.2, U16.7 (D2)
LVDS_SPI_TX_CSN: R137.2, U16.4 (D1)
LVDS_SPI_TX_MISO: R131.2, U16.12 (D4)
LVDS_SPI_TX_MOSI: R128.2, U16.9 (D3)
MCP16502_HPM: R79.1, R156.2, R169.2, R177.1
MCP16502_INT_PD9: R86.2, U6.1 (nINTO), U8.D19 (PD9)
MICRO-USB_DEBUG_USB_N: U17.8 (HSD2-), U19.2 (D-)
MICRO-USB_DEBUG_USB_P: U17.9 (HSD2+), U19.3 (D+)
MICRO-USB_DEBUG_VBUS: D11.2 (A), R270.1, U19.1 (VBUS)
MICRO-USB_EXP_USB_N: U18.8 (HSD2-), U20.2 (D-)
MICRO-USB_EXP_USB_P: U18.9 (HSD2+), U20.3 (D+)
MICRO-USB_EXP_VBUS: D12.2 (A), R272.1, U20.1 (VBUS)
NRST: C94.2, R171.2, R296.2
NTC1-: J19.2, R283.1, R284.1
NTC2-: J19.4, R280.1, R281.1
NTC3-: J19.6, R286.1, R287.1
NTC4-: J19.8, R289.1, R290.1
unnamed: C90.2, JP3.1, R114.2
unnamed: C91.2, JP4.1, R115.1, R116.2
unnamed: C187.2, R303.2, R304.2, R305.1
unnamed: C190.2, R307.2, R308.2, R309.1
unnamed: C241.2, JP14.1, R368.1, R370.2
unnamed: C242.2, JP15.1, R369.1, R371.2
unnamed: D2.2 (A), R1.2
unnamed: D3.2 (A), R9.2
unnamed: C8.2, D4.1 (K), L1.1, U2.8 (PH)
unnamed: D5.2 (A), R11.2
unnamed: D6.2 (A), R12.2
unnamed: D7.2 (A), R15.2
unnamed: D8.1 (K), R23.1
unnamed: D9.1 (K), R53.2
unnamed: D10.2 (A), R52.2
unnamed: D11.1 (K), R274.2
unnamed: D12.1 (K), R275.2
unnamed: D13.2 (A), R325.2
unnamed: D14.2 (A), R326.2
unnamed: D15.2 (A), R327.2
unnamed: D16.2 (A), R328.2
unnamed: D18.2 (A), R329.2
unnamed: D19.2 (A), R336.2
unnamed: D20.2 (A), R338.2
unnamed: D20.1 (K), Q2.C
unnamed: D21.2 (A), R342.2
unnamed: D21.1 (K), Q3.C
unnamed: D22.2 (A), R346.2
unnamed: D22.1 (K), Q4.C
unnamed: D23.2 (A), R386.2
unnamed: D24.2 (A), R387.2
unnamed: D24.1 (K), Q5.C
unnamed: D25.2 (A), R388.2
unnamed: DNP/U10.1 (nCS), JP6.1, R245.2, R246.2
unnamed: J6.06, R33.1
unnamed: J6.09, R35.2
unnamed: J6.11, R37.2
unnamed: J6.13, R39.2
unnamed: J6.14, R40.1
unnamed: J6.15, R42.2
unnamed: J6.21, R44.2
unnamed: J6.23, R45.2
unnamed: J6.25, R46.2
unnamed: J6.27, R47.2
unnamed: J6.37, R50.2
unnamed: J6.38, R51.1
unnamed: J6.39, R54.2
unnamed: J6.41, R55.2
unnamed: J6.43, R56.2, R64.1
unnamed: J6.44, R57.1
unnamed: J6.45, R59.2, R65.1
unnamed: J6.46, R60.1
unnamed: JP2.1, R8.2, R10.1
unnamed: JP2.2, R9.1
unnamed: JP7.1, R259.2, R260.1
unnamed: JP7.2, R258.2
unnamed: J17.1, JP8.2 (B)
unnamed: JP9.1 (A), R298.1
unnamed: JP9.2 (B), R299.1, U25.3 (DELAY/MRST)
unnamed: Q2.B, R339.1, R341.1
unnamed: Q3.B, R343.1, R345.1
unnamed: Q4.B, R347.1, R348.1
unnamed: Q5.B, R391.1
unnamed: R201.2, R204.2, R209.1
unnamed: R203.2, R205.2, R211.1
unnamed: C6.2, U1.7 (DVDT)
unnamed: C5.2, U1.10 (ITIMER)
unnamed: R2.2, R6.1, U1.2 (OVLO/OVCSEL)
unnamed: C8.1, U2.1 (BOOT)
unnamed: R13.2, R14.1, U2.4 (VSENSE)
unnamed: R20.1, U5.6 (ADDRSEL)
unnamed: R18.2, U5.16 (~PWRDN)
unnamed: R79.2, U6.23 (HPM)
unnamed: R76.2, U6.22 (LPM)
unnamed: R80.2, U6.8 (PWRHLD)
unnamed: R88.2, R90.1, U6.18 (SELVL1)
unnamed: L2.1, U6.11 (SW1)
unnamed: L3.1, U6.14 (SW2)
unnamed: L4.1, U6.27 (SW3)
unnamed: L5.1, U6.30 (SW4)
unnamed: R83.1, U7.6 (ADDRSEL)
unnamed: R81.2, U7.16 (~PWRDN)
unnamed: R143.1, U8.AA19 (PIOBU0)
unnamed: R146.1, U8.P9 (PIOBU1)
unnamed: R95.1, U8.C6 (HHSA_RTUNE)
unnamed: R98.1, U8.D8 (HHSB_RTUNE)
unnamed: R100.1, U8.B7 (HHSC_RTUNE)
unnamed: R97.2, U8.W15 (JTAGSEL)
unnamed: R99.2, U8.R10 (LPM)
unnamed: R105.1, U8.R19 (MIPI_REXT)
unnamed: R101.2, U8.P16 (QSPI0_CAL)
unnamed: R102.2, U8.K15 (SDMMC0_CAL)
unnamed: R103.2, U8.J10 (SDMMC1_CAL)
unnamed: R104.2, U8.D14 (SDMMC2_CAL)
unnamed: R233.2, U9.L8 (ZQ)
unnamed: C142.2, C143.2, U13.E4 (VDDIM)
unnamed: R263.1, U14.6 (INH)
unnamed: R268.1, U15.15 (nEN)
unnamed: R269.1, U16.15 (nEN)
unnamed: R270.2, R271.1, U17.2 (SEL)
unnamed: R272.2, R273.1, U18.2 (SEL)
unnamed: R278.1, U21.2 (VOUT)
unnamed: C163.2, R280.2, U22.3 (+)
unnamed: R279.1, U22.1, U22.2 (-)
unnamed: R282.1, U22.5 (+), U22.7
unnamed: C167.2, R283.2, U22.6 (-)
unnamed: C169.2, R286.2, U23.3 (+)
unnamed: R285.1, U23.1, U23.2 (-)
unnamed: R288.1, U23.5 (+), U23.7
unnamed: C173.2, R289.2, U23.6 (-)
unnamed: R293.2, U24.1 (CLKOE)
unnamed: R300.1, U25.4 (DONE)
unnamed: R297.1, U25.5 (WAKE)
unnamed: R296.1, U25.6 (~RST)
unnamed: R306.1, U30.8 (RS)
unnamed: R304.1, U30.5 (VREF)
unnamed: R310.1, U31.8 (RS)
unnamed: R308.1, U31.5 (VREF)
unnamed: C191.2, U32.9 (CAP)
unnamed: R312.2, U32.15 (ENV_SCL)
unnamed: R311.2, U32.16 (ENV_SDA)
unnamed: R320.2, R321.2, U33.7 (~SLO)
unnamed: C205.2, U35.7 (DVDT)
unnamed: C204.2, U35.10 (ITIMER)
unnamed: R331.2, R335.1, U35.2 (OVLO/OVCSEL)
unnamed: R340.2, U37.3 (EN)
unnamed: R344.2, U38.3 (EN)
unnamed: R349.2, U39.3 (EN)
unnamed: R360.1, U40.F6 (PB24A)
unnamed: R361.1, U40.F5 (PB24B)
unnamed: R358.1, U40.F8 (PB26A)
unnamed: R357.1, U40.F9 (PB26B)
unnamed: R365.1, U40.E6 (PB28A)
unnamed: R366.1, U40.E5 (PB28B)
unnamed: R364.1, U40.E7 (PB30A)
unnamed: R359.1, U40.F7 (PB30B)
unnamed: R355.1, U40.G5 (PB60A)
unnamed: R379.2, U40.K7 (PB56A)
unnamed: R377.1, U40.L7 (PB56B)
unnamed: R373.2, U40.H5 (PB60B)
unnamed: R372.2, U40.H4 (PB66A)
unnamed: R376.2, U40.J4 (PB66B)
unnamed: R374.2, U40.J1 (PB68A)
unnamed: R375.2, U40.J2 (PB68B)
unnamed: FB2.1, U41.6 (VDD)
unnamed: R384.2, U42.2 (DIR1)
unnamed: R381.2, U42.11 (DIR2)
unnamed: R383.2, U42.22 (~OE)
unnamed: R399.2, R401.2, U43.1 (CS#)
unnamed: R397.2, R403.1, U43.7 (IO3/RESET#)
unnamed: R405.1, U43.5 (SI/IO0)
unnamed: R402.2, U43.2 (SO/IO1)
unnamed: R400.2, R404.2, U43.3 (WP#/IO2)
unnamed: R398.1, U44.15 (nEN)
unnamed: R110.1, Y3.3 (OUT)
unnamed: R112.1, Y4.3 (OUT)
unnamed: R367.1, Y6.3 (OUT)
unnamed: R363.2, Y6.1 (~STB)
OSC_LVDS_ENABLE: R382.1, U40.B3 (PT67A), U41.1 (EN)
OSC_LVDS_N: R385.2, U40.G11 (PB20B), U41.5 (OUT-)
OSC_LVDS_P: R385.1, U40.G10 (PB20A), U41.4 (OUT)
OSC_STBY: Q1.3 (D), R91.2, Y4.1 (~STB)
PAC1934_INT_PC8: R82.2, R198.2, U7.1 (SLOW/~ALERT)
PAC1934_INT_PE2: R19.2, R125.2, U5.1 (SLOW/~ALERT)
PHY_LVDS_RXC_N: J9.9, R302.2, U29.4 (IN-)
PHY_LVDS_RXC_P: J9.8, R302.1, U29.3 (IN+)
PHY_LVDS_RXD_N: J9.4, R301.2, U28.4 (IN-)
PHY_LVDS_RXD_P: J9.3, R301.1, U28.3 (IN+)
PHY_LVDS_TXC_N: J9.7, U27.3 (OUT-)
PHY_LVDS_TXC_P: J9.6, U27.4 (OUT+)
PHY_LVDS_TXD_N: J9.2, U26.3 (OUT-)
PHY_LVDS_TXD_P: J9.1, U26.4 (OUT+)
POW_ONOFF_FPGA: R122.2, R330.2, R334.1, U35.1 (EN/UVLO)
RS_422_RX+: JP10.1 (A), R34.1, R43.2, R322.1, U33.11 (A)
RS_422_RX-: JP11.1 (A), R32.1, R41.2, R322.2, U33.10 (B)
RS_422_TX+: JP10.2 (B), R30.1, R36.2, R323.2, U33.8 (Y)
RS_422_TX-: JP11.2 (B), R31.1, R38.2, R323.1, U33.9 (Z)
RTC_CLOCK: R197.2, R294.2, U24.3 (CLKOUT)
RTC_INT: R143.2, R295.2, U24.7 (~INT)
SAM7_FLEX1_I2C_SCL: R16.2, R77.2, R202.2, R291.2, U5.4 (SM_CLK), U6.6 (SCL), U7.4 (SM_CLK), U24.4 (SCL)
SAM7_FLEX1_I2C_SDA: R17.2, R78.2, R200.2, R292.2, U5.5 (SM_DATA), U6.5 (SDA), U7.5 (SM_DATA), U24.5 (SDA)
SAMA7_FLASH_SPI_FPGA_SEL: R161.2, R395.2, U44.1 (SEL)
SAMA7_FLASH_SPI_MCLK: R133.2, U44.5 (S2A)
SAMA7_FLASH_SPI_MCSN: R136.2, R393.2, U44.2 (S1A)
SAMA7_FLASH_SPI_MISO/MD1: R130.2, U44.14 (S4A)
SAMA7_FLASH_SPI_MOSI/MD0: R127.2, U44.11 (S3A)
SAMA7_FPGA_HEATBEAT: R195.2, R386.1, U42.14 (B8)
SAMA7_FPGA_INT_ERROR: R194.2, U42.15 (B7)
SAMA7_LVDS_SPI_RX_SEL: R162.2, R264.2, U15.1 (SEL)
SAMA7_LVDS_SPI_TX_SEL: R164.2, R266.2, U16.1 (SEL)
SAMA7_SPARE_IN1: R213.2, U42.19 (B3)
SAMA7_SPARE_IN2: R196.2, U42.18 (B4)
SAMA7_SPI_RX_AVAIL: R190.2, U42.16 (B6)
SAMA7_SPI_RX_CSN: R265.2, U15.3 (S1B), U42.20 (B2)
SAMA7_SPI_TX_CSN: R267.2, U16.3 (S1B), U42.21 (B1)
SAMA7_SPI_TX_READY: R189.2, U42.17 (B5)
SAM_AX100U_I2C_SCL: J11.05, R66.1, R207.2
SAM_AX100U_I2C_SDA: J11.06, R67.1, R210.2
SAM_BNO_RX: U14.4 (2Y3), U32.20 (H_SDA/H_MISO/TX)
SAM_BNO_TX: U14.11 (1Y3), U32.19 (H_SCL/SCK/RX)
SAM_HOST_UART_RXD: J12.11, U14.1 (2Y0)
SAM_HOST_UART_TXD: J12.12, U14.12 (1Y0)
SAM_LVDS_RXC_SPI_SCK: U15.5 (S2A), U29.5 (TTL_IN)
SAM_LVDS_RXD_SPI_MISO: U15.14 (S4A), U28.5 (TTL_IN)
SAM_LVDS_TXC_SPI_SCK: U16.5 (S2A), U27.5 (TTL_IN)
SAM_LVDS_TXD_SPI_MOSI: U16.11 (S3A), U26.5 (TTL_IN)
SAM_OEM719_PPS: J12.19, R40.2, R159.2
SAM_OEM719_UART_RX: J12.14, R54.1, U14.5 (2Y1)
SAM_OEM719_UART_TX: J12.15, R55.1, U14.14 (1Y1)
SD2_CLK: J16.P5 (CLK), R178.2, R243.2, U11.3 (IO2)
SD2_CMD: J16.P3 (CMD), R176.2, R244.2, U12.1 (IO1)
SD2_DATA0: J16.P7 (DAT0), R180.2, R240.2, U11.4 (IO3)
SD2_DATA1: J16.P8 (DAT1), R183.2, R239.2, U11.6 (IO4)
SD2_DATA2: J16.P1 (DAT2), R185.2, R241.2, U12.4 (IO3)
SD2_DATA3: J16.P2 (CD/DAT3), R188.2, R242.2, U12.6 (IO4)
SD2_nCD: J16.P9 (DET), R191.2, R238.2
SHDN: R80.1, U8.R9 (SHDN)
SOM_CANRX0: R208.2, U30.4 (R)
SOM_CANRX1: R214.2, U31.4 (R)
SOM_CANTX0: R206.2, U30.1 (D)
SOM_CANTX1: R212.2, U31.1 (D)
SOM_CONSOLE_RX: J18.3, R218.2, R277.2
SOM_CONSOLE_TX: J18.2, R216.2, R276.2
SOM_EMMC_nRST: R123.2, R257.2, U13.M5 (RST_n)
SOM_MRAM_QSPI_CLK: DNP/U10.6 (CLK), R155.2
SOM_MRAM_QSPI_IO0: DNP/U10.5 (SI/IO[0]), R150.2
SOM_MRAM_QSPI_IO1: DNP/U10.2 (SO/IO[1]), R148.2
SOM_MRAM_QSPI_IO2: DNP/U10.3 (nWP/IO[2]), R145.2
SOM_MRAM_QSPI_IO3: DNP/U10.7 (IO[3]), R142.2
SOM_RAM_QSPI_nCS: R153.2, R246.1
SOM_RS422_DE: R232.2, R324.1, U33.3 (DE)
SOM_RS422_RX: R231.2, U33.1 (RO)
SOM_RS422_TX: R230.2, U33.4 (DI)
SOM_RS422_~RE: R119.2, R319.2, U33.2 (~RE)
SOM_SDMMC0_CD_PA14: R154.2, R259.1
SOM_SDMMC0_OUT_CK: R117.2, R256.2, U13.P6 (CLK)
SOM_SDMMC0_OUT_CMD: R120.2, R255.2, U13.P5 (CMD)
SOM_SDMMC0_OUT_D0: R126.2, R254.2, U13.K2 (DAT0)
SOM_SDMMC0_OUT_D1: R129.2, R253.2, U13.N2 (DAT1)
SOM_SDMMC0_OUT_D2: R132.2, R252.2, U13.K3 (DAT2)
SOM_SDMMC0_OUT_D3: R135.2, R251.2, U13.N3 (DAT3)
SOM_SDMMC0_OUT_D4: R138.2, R250.2, U13.N8 (DAT4)
SOM_SDMMC0_OUT_D5: R139.2, R249.2, U13.K8 (DAT5)
SOM_SDMMC0_OUT_D6: R141.2, R248.2, U13.N9 (DAT6)
SOM_SDMMC0_OUT_D7: R144.2, R247.2, U13.K9 (DAT7)
SOM_SDMMC0_OUT_DS: R147.2, U13.K5 (DS)
SOM_STATUS_LED_1: R151.2, R326.1
SOM_STATUS_LED_2: R224.2, R325.1
SOM_STATUS_LED_3: R140.2, R327.1
SOM_USER_BUTTON_PA12: R116.1, R149.2
SPI_CLK_EXP: R71.1, R172.2
SPI_CS_EXP: R70.1, R173.2
SPI_MISO_EXP: R75.1, R175.2
SPI_MOSI_EXP: R73.1, R174.2
STX_12V: J7.23, J7.24
STX_GPIO_EN: R33.2, R165.2
SYS_PLL_INPUT: R367.2, U40.E3 (PR13A)
SubSPW_LVDS_DIN_N: J21.4, R376.1, R378.1
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

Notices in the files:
parts and their libraries:
Copyright: Copyright (C) 2025 Ultra Librarian. All rights reserved.
Copyright: Copyright (C) 2026 Ultra Librarian. All rights reserved.
